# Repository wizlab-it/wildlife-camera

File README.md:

# Wildlife Camera

Battery-powered wildlife camera.
Based on the ESP32-CAM board. Wi-Fi support.
Takes pictures when movements are detected via a PIR sensor.
Stores pictures on SD Card (if present) and sends them to Telegram (if Wi-Fi available).
Controlled via telegram commands (if Wi-Fi available).

Documentation is incomplete, sorry for that.

## Telegram API Reference

You need first to create a bot via the @BotFather telegram bot.
You can find many websites that explains how to do that.
Add these commands to the bot: /wakeup, /photo, /photoflash, /status, /blink

### Get Updates
#### Get all unconfirmed updates (max 100)
```
curl "https://api.telegram.org/bot{API_TOKEN}/getUpdates"
```
#### Get last unconfirmed update
```
curl "https://api.telegram.org/bot{API_TOKEN}/getUpdates?offset=-1"
```
#### Get updates starting from the specified one
```
curl "https://api.telegram.org/bot{API_TOKEN}/getUpdates?offset={OFFSET_ID}"
```
### Post Messages
```
curl -s -X POST "https://api.telegram.org/bot{API_TOKEN}/sendMessage" -d chat_id={CHAT_ID} -d text="{MESSAGE}"
```

## Required libraries
- CRC32 by Christopher Baker
- ArduinoJson by Benoit Blanchon
- UrlEncode by Masayuki

## Online references
- [Telegram bot API](https://core.telegram.org/bots/api)
- [Telegram getUpdates API command](https://telegram-bot-sdk.readme.io/reference/getupdates)
- [ESP32 Documentation](https://docs.espressif.com/projects/arduino-esp32/)

## Credits and references
Created by [WizLab.it](https://www.wizlab.it/)
GitHub: [wizlab-it/wildlife-camera](https://github.com/wizlab-it/wildlife-camera/)

## License
This program is free software: you can redistribute it and/or modify it under the terms of the GNU General Public License as published by the Free Software Foundation, either version 3 of the License, or (at your option) any later version.
This program is distributed in the hope that it will be useful, but WITHOUT ANY WARRANTY; without even the implied warranty of MERCHANTABILITY or FITNESS FOR A PARTICULAR PURPOSE. See the GNU General Public License for more details.
To get a copy of the GNU General Public License, see [http://www.gnu.org/licenses/](http://www.gnu.org/licenses/)

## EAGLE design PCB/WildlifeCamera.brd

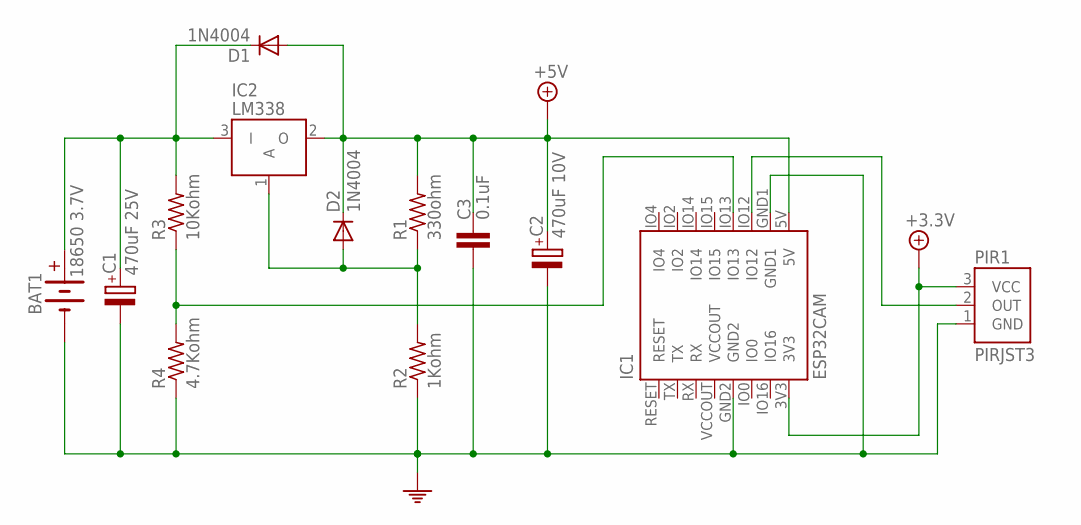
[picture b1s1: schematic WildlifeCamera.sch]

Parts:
BAT1: 18650 3.7V; SIL2
C1: 470uF 25V; CAPACITOR-5MM
C2: 470uF 10V; CAPACITOR-5MM
C3: 0.1uF; CAPACITOR-5MM
D1, D2: 1N4004; DIODE-BIG
IC1: ESP32CAM
IC2: LM338; TO220
PIR1: PIRJST3; JST3
R1: 330ohm; RESISTOR-0.25W
R2: 1Kohm; RESISTOR-0.25W
R3: 10Kohm; RESISTOR-0.25W
R4: 4.7Kohm; RESISTOR-0.25W

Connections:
+3.3V: IC1.3V3, PIR1.3 (VCC)
+5V: C2.1, C3.1, D1.A, D2.C, IC1.5V, IC2.2 (O), R1.2
GND: BAT1.2 (-), C1.2, C2.2, C3.2, IC1.GND1, IC1.GND2, PIR1.1 (GND), R2.1, R4.1
unnamed: BAT1.1 (+), C1.1, D1.C, IC2.3 (I), R3.2
unnamed: IC1.IO13, R3.1, R4.2
unnamed: D2.A, IC2.1 (A), R1.1, R2.2
unnamed: IC1.IO12, PIR1.2 (OUT)
VCCOUT: IC1.VCCOUT

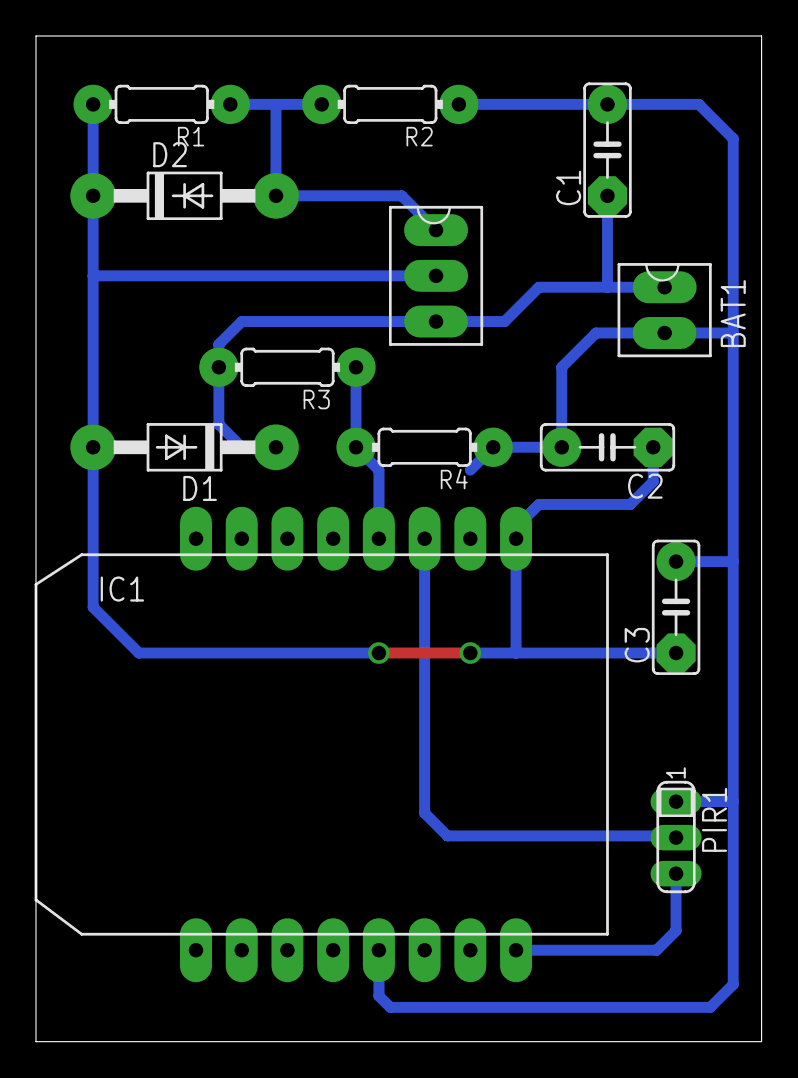
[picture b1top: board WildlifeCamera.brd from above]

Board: 2 copper layers, 40.3 x 55.9 mm, 13 parts (0 on the bottom side), 7 nets.
